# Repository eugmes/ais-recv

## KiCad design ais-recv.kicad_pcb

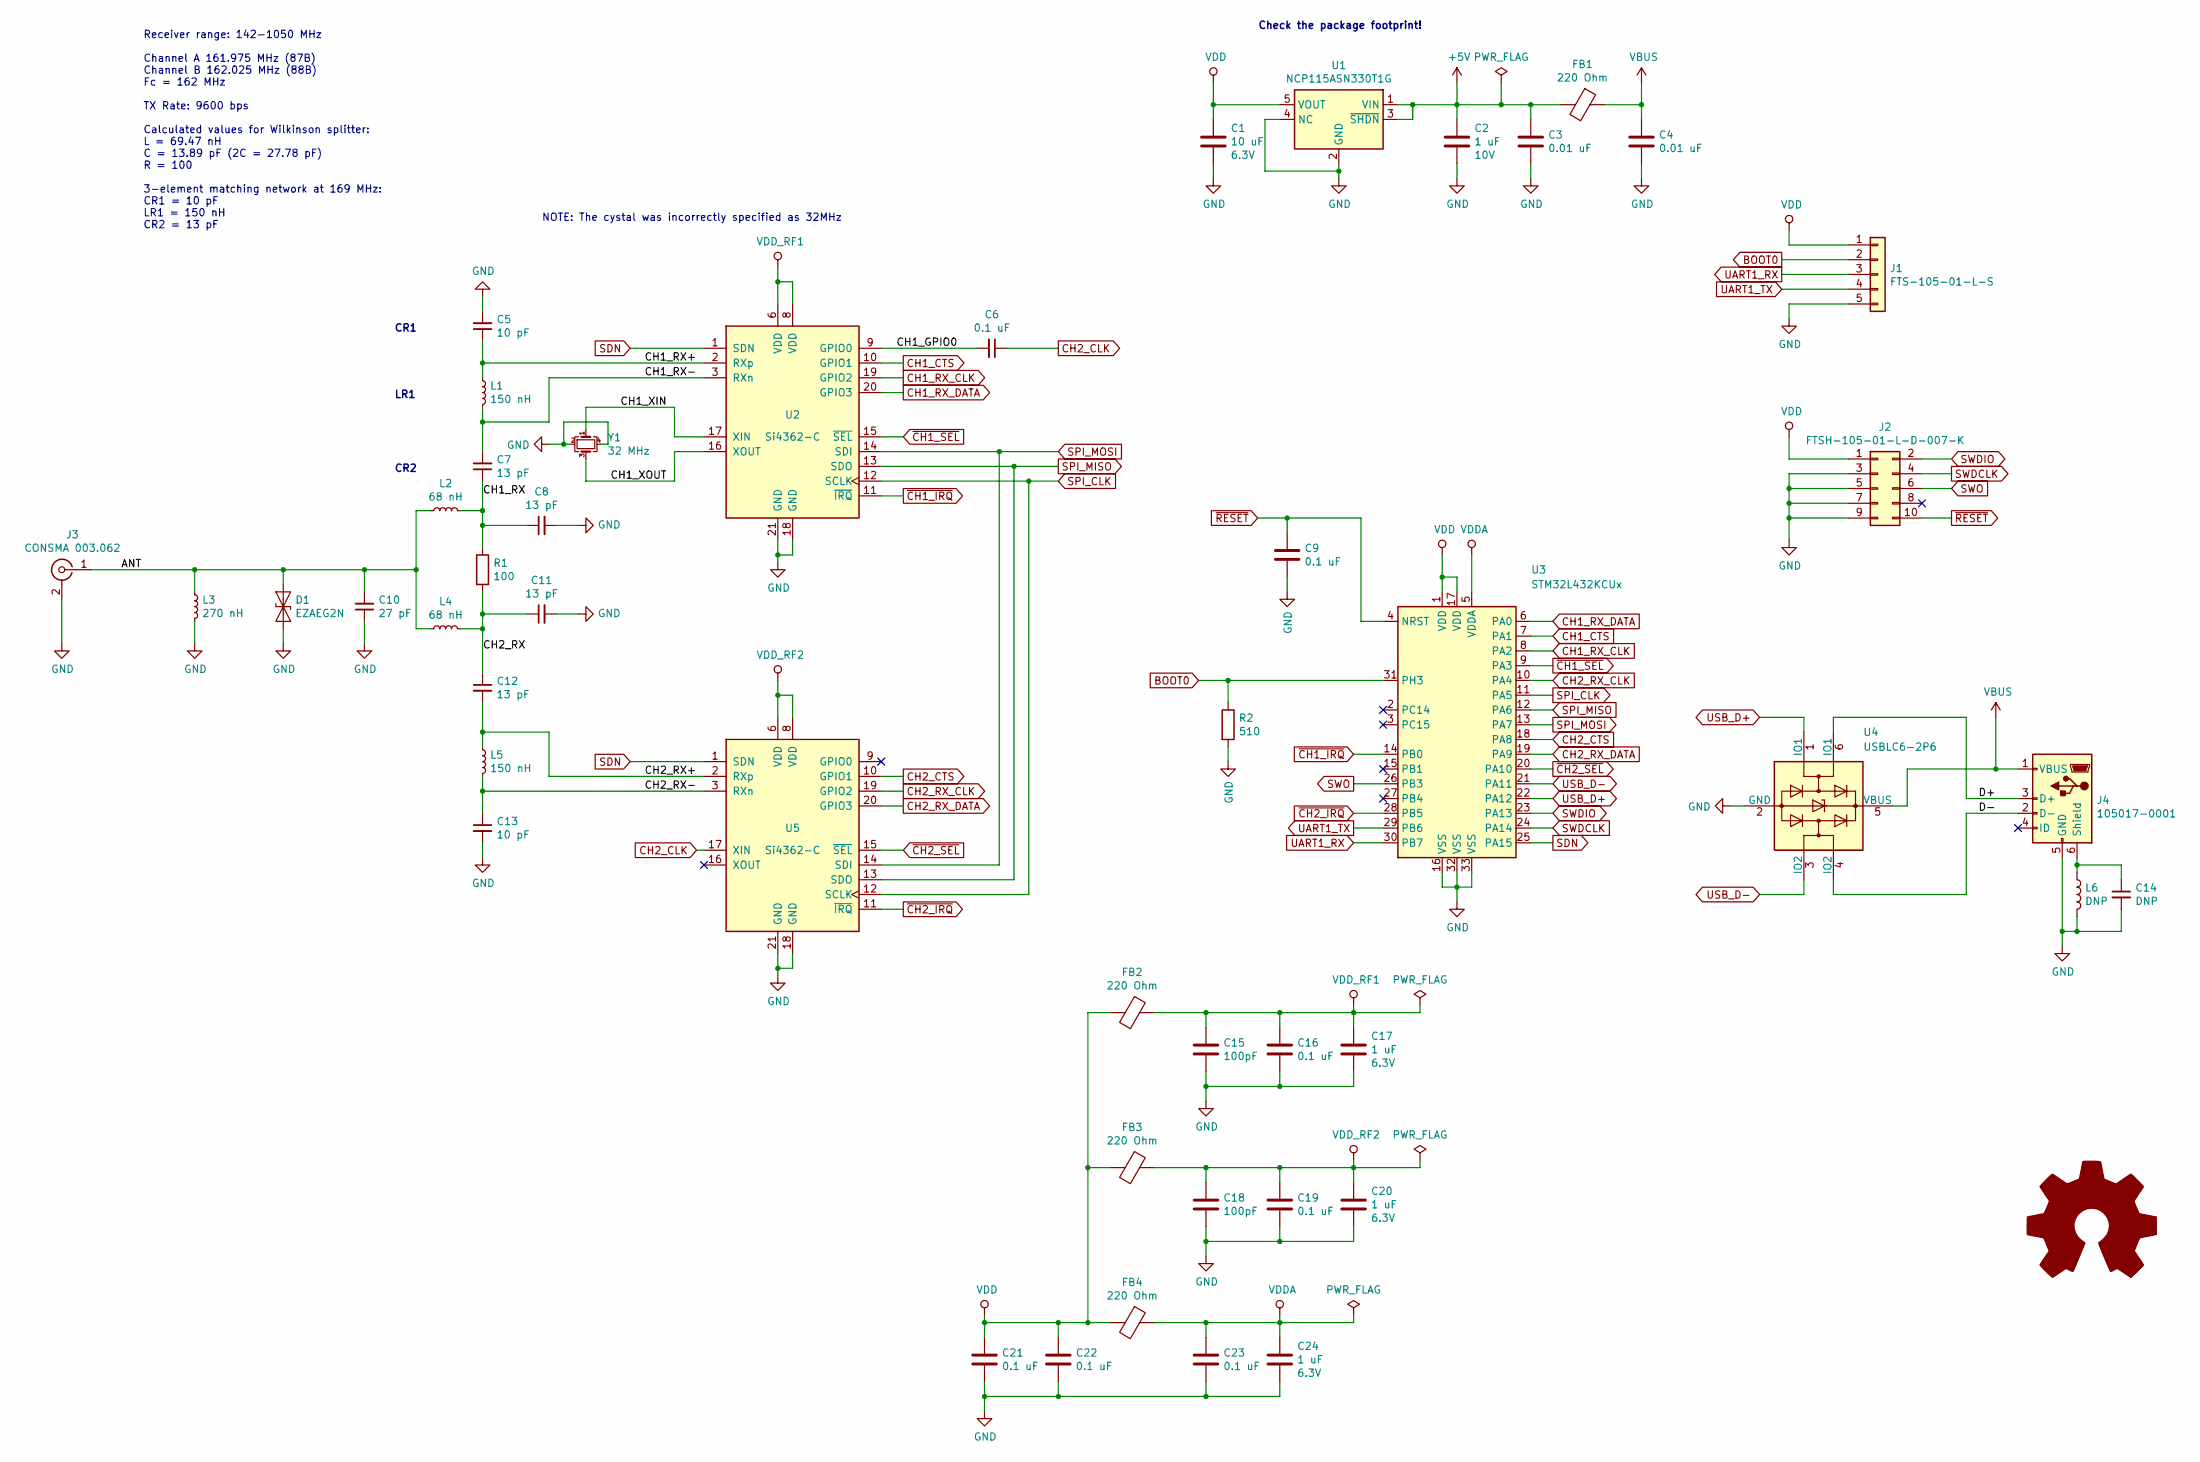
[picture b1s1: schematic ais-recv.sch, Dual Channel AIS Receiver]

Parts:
C1: 10 uF; CAPC1608X55; Voltage Rating 6.3V
C2: 1 uF; CAPC1608X55; Voltage Rating 10V
C3, C4: 0.01 uF; CAPC1005X55
C5, C13: 10 pF; CAPC1005X55
C6, C9, C16, C19, C21, C22, C23: 0.1 uF; CAPC1005X55
C7, C8, C11, C12: 13 pF; CAPC1005X55
C10: 27 pF; CAPC1005X55
C14: DNP; CAPC1005X55
C15, C18: 100pF; CAPC1005X55
C17, C20, C24: 1 uF; CAPC1005X55; Voltage Rating 6.3V
D1: EZAEG2N; INDC1005X60; MFG Part Num EZAEG2N
FB1, FB2, FB3, FB4: 220 Ohm; INDC1005X60; MFG Part Num MPZ1005S221HT000
J1: FTS-105-01-L-S; PinHeader_1x05_P1.27mm_Vertical; MFG Part Num FTS-105-01-L-S
J2: FTSH-105-01-L-D-007-K; PinHeader_2x05_P1.27mm_Vertical; MFG Part Num FTSH-105-01-L-D-007-K
J3: CONSMA 003.062; SMA_Linx_CONSMA_003_062; MFG Part Num CONSMA 003.062
J4: 105017-0001; USB_Micro-B_Molex-105017-0001; MFG Part Num 105017-0001
L1, L5: 150 nH; INDC1005X60
L2, L4: 68 nH; INDC1005X60
L3: 270 nH; INDC1005X60
L6: DNP; INDC1005X60
LOGO1: Logo_Open_Hardware_Large; OSHW-Symbol_6.7x6mm_SilkScreen
R1: 100; RESC1005X40
R2: 510; RESC1005X40
U1: NCP115ASN330T1G; TSOP-5_1.65x3.05mm_P0.95mm
U2, U5: Si4362-C; QFN50P400X400X80-21B-THERMALVIAS
U3: STM32L432KCUx; QFN50P500X500X80-33-THERMALVIAS
U4: USBLC6-2P6; SOT-666; MFG Part Num USBLC6-2P6
Y1: 32 MHz; OSCCC200X250X080; MFG Part Num ECS-320-12-36B-CTN-TR

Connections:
+5V: C2.1, C3.1, FB1.2, U1.1 (VIN), U1.3 (~SHDN)
/ANT: C10.2, D1.1 (A1), J3.1 (In), L2.1, L3.1, L4.1
/CH1_GPIO0: C6.2, U2.9 (GPIO0)
/CH1_RX: C7.1, C8.1, L2.2, R1.1
/CH1_RX+: C5.1, L1.2, U2.2 (RXp)
/CH1_RX-: C7.2, L1.1, U2.3 (RXn)
/CH1_XIN: U2.17 (XIN), Y1.1
/CH1_XOUT: U2.16 (XOUT), Y1.3
/CH2_RX: C11.1, C12.1, L4.2, R1.2
/CH2_RX+: C12.2, L5.1, U5.2 (RXp)
/CH2_RX-: C13.1, L5.2, U5.3 (RXn)
/D+: J4.3 (D+), U4.6 (IO1)
/D-: J4.2 (D-), U4.4 (IO2)
BOOT0: J1.2, R2.1, U3.31 (PH3)
CH1_CTS: U2.10 (GPIO1), U3.7 (PA1)
CH1_RX_CLK: U2.19 (GPIO2), U3.8 (PA2)
CH1_RX_DATA: U2.20 (GPIO3), U3.6 (PA0)
CH2_CLK: C6.1, U5.17 (XIN)
CH2_CTS: U3.18 (PA8), U5.10 (GPIO1)
CH2_RX_CLK: U3.10 (PA4), U5.19 (GPIO2)
CH2_RX_DATA: U3.19 (PA9), U5.20 (GPIO3)
GND: C1.2, C2.2, C3.2, C4.2, C5.2, C8.2, C9.2, C10.1, C11.2, C13.2, C14.2, C15.2, C16.2, C17.2, C18.2, C19.2, C20.2, C21.2, C22.2, C23.2, C24.2, D1.2 (A2), J1.5, J2.3, J2.5, J2.7, J2.9, J3.2 (Ext), J4.5 (GND), L3.2, L6.2, R2.2, U1.2 (GND), U1.4 (NC), U2.18 (GND), U2.21 (GND), U3.16 (VSS), U3.32 (VSS), U3.33 (VSS), U4.2 (GND), U5.18 (GND), U5.21 (GND), Y1.2, Y1.4
unnamed: C14.1, J4.6 (Shield), L6.1
SDN: U2.1 (SDN), U3.25 (PA15), U5.1 (SDN)
SPI_CLK: U2.12 (SCLK), U3.11 (PA5), U5.12 (SCLK)
SPI_MISO: U2.13 (SDO), U3.12 (PA6), U5.13 (SDO)
SPI_MOSI: U2.14 (SDI), U3.13 (PA7), U5.14 (SDI)
SWDCLK: J2.4, U3.24 (PA14)
SWDIO: J2.2, U3.23 (PA13)
SWO: J2.6, U3.26 (PB3)
UART1_RX: J1.3, U3.30 (PB7)
UART1_TX: J1.4, U3.29 (PB6)
USB_D+: U3.22 (PA12), U4.1 (IO1)
USB_D-: U3.21 (PA11), U4.3 (IO2)
VBUS: C4.1, FB1.1, J4.1 (VBUS), U4.5 (VBUS)
VDD: C1.1, C21.1, C22.1, FB2.2, FB3.2, FB4.2, J1.1, J2.1, U1.5 (VOUT), U3.1 (VDD), U3.17 (VDD)
VDDA: C23.1, C24.1, FB4.1, U3.5 (VDDA)
VDD_RF1: C15.1, C16.1, C17.1, FB2.1, U2.6 (VDD), U2.8 (VDD)
VDD_RF2: C18.1, C19.1, C20.1, FB3.1, U5.6 (VDD), U5.8 (VDD)
~CH1_IRQ: U2.11 (~IRQ), U3.14 (PB0)
~CH1_SEL: U2.15 (~SEL), U3.9 (PA3)
~CH2_IRQ: U3.28 (PB5), U5.11 (~IRQ)
~CH2_SEL: U3.20 (PA10), U5.15 (~SEL)
~RESET: C9.1, J2.10, U3.4 (NRST)

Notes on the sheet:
Receiver range: 142-1050 MHz Channel A 161.975 MHz (87B) Channel B 162.025 MHz (88B) Fc = 162 MHz TX Rate: 9600 bps Calculated values for Wilkinson splitter: L = 69.47 nH C = 13.89 pF (2C = 27.78 pF) R = 100 3-element matching network at 169 MHz: CR1 = 10 pF LR1 = 150 nH CR2 = 13 pF
CR2
LR1
CR1
Check the package footprint!
NOTE: The cystal was incorrectly specified as 32MHz

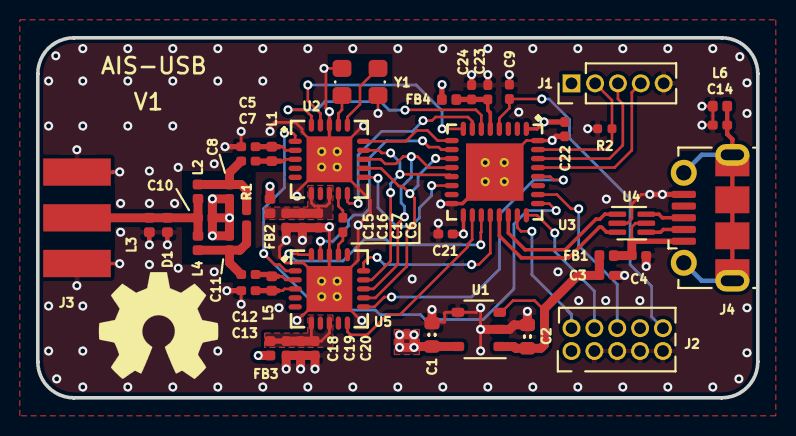
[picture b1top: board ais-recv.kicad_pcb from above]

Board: 4 copper layers, 40.0 x 20.0 mm, 48 parts (0 on the bottom side), 44 nets.

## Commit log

2020-07-23 Initial version using STM32L072KZUx
    The layout is incomplete.
2020-07-23 Use STML4
2020-07-26 Changes for version 1.0
2020-07-26 Add schematic in PDF format
2020-07-26 Add board rendering
2020-08-30 Fix part numbers for the debug connector, USB ESD diodes, quartz
    Add a note about wrong quartz frequency.
2020-08-30 Add pads on the bottom of the SMA connector
2020-09-22 Remove a note about checking a footprint
    The footprint is correct.
